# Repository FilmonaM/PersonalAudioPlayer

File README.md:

# Personal Audio Player

## Project Overview
A pocket-sized, RP2040-based audio player featuring:
- **Adafruit Feather RP2040 Adalogger** (built-in microSD slot & Li-Po charger)
- **Adafruit PCM5102A DAC** breakout board that also includes audio jack
- **2.4″ SSD1309 128×64 OLED** display (I²C)
- **Six 6 × 6 mm tactile buttons** for menu navigation & transport controls
- **One 10 kΩ potentiometer** for volume control
- no firmware...yet
---
## Case

## PCB 

## Schematic

---
## BOM

| item | quantity                                   | link                                      |
|----:|--------------------------------------------------|--------------------------------------------|
| rp2040 adalogger  | 1 |  [link](https://www.adafruit.com/product/5980?srsltid=AfmBOoo8XiFZ5O-aQrgWYq57rMrMTgJX_qIoyT-_eMKxOjlOtefi_cEq) |
| pcm5102a  | 1 |  [link](https://www.adafruit.com/product/6250?srsltid=AfmBOoqd1F7VRiLRdiD3oSu3U9al2WLzJexfJeOLYhPyQlxJku6weyUe)     |
| 2.4" oled display | 1  | [link](https://www.adafruit.com/product/6250?srsltid=AfmBOoqd1F7VRiLRdiD3oSu3U9al2WLzJexfJeOLYhPyQlxJku6weyUe)   |
| pushbutton switches   | 6  | I have my own  |
| 10kohm potentiometer | 1    | I have my own  |
| PCB | 5|     |
|lipo-battery| 1| I have my own

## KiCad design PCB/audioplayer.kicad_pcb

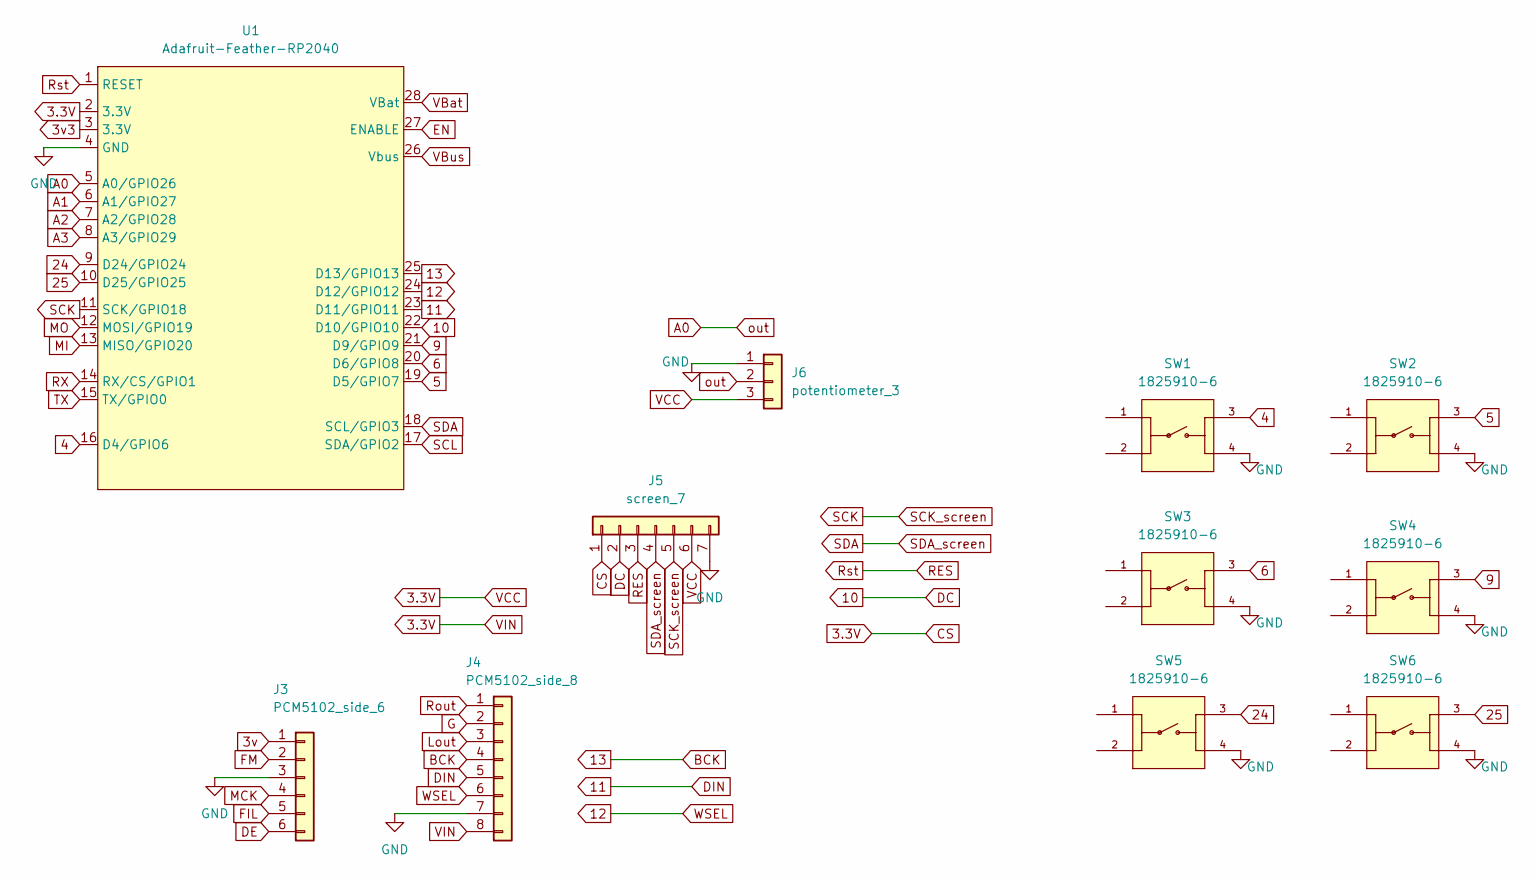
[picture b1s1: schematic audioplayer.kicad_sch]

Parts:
J3: PCM5102_side_6; PinHeader_1x06_P2.54mm_Vertical
J4: PCM5102_side_8; PinHeader_1x08_P2.54mm_Vertical
J5: screen_7; PinHeader_1x07_P2.54mm_Vertical
J6: potentiometer_3; PinHeader_1x03_P2.54mm_Vertical
SW1, SW2, SW3, SW4, SW5, SW6: 1825910-6; SW_1825910-6-4; PARTREV C10
U1: Adafruit-Feather-RP2040

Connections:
3.3V: J4.8, J5.1, J5.6, J6.3, U1.2 (3.3V)
3v: J3.1
3v3: U1.3 (3.3V)
4: SW1.3, U1.16 (D4/GPIO6)
5: SW2.3, U1.19 (D5/GPIO7)
6: SW3.3, U1.20 (D6/GPIO8)
9: SW4.3, U1.21 (D9/GPIO9)
10: J5.2, U1.22 (D10/GPIO10)
11: J4.5, U1.23 (D11/GPIO11)
12: J4.6, U1.24 (D12/GPIO12)
13: J4.4, U1.25 (D13/GPIO13)
24: SW5.3, U1.9 (D24/GPIO24)
25: SW6.3, U1.10 (D25/GPIO25)
A0: J6.2, U1.5 (A0/GPIO26)
A1: U1.6 (A1/GPIO27)
A2: U1.7 (A2/GPIO28)
A3: U1.8 (A3/GPIO29)
DE: J3.6
EN: U1.27 (ENABLE)
FIL: J3.5
FM: J3.2
G: J4.2
GND: J3.3, J4.7, J5.7, J6.1, SW1.4, SW2.4, SW3.4, SW4.4, SW5.4, SW6.4, U1.4 (GND)
Lout: J4.3
MCK: J3.4
MI: U1.13 (MISO/GPIO20)
MO: U1.12 (MOSI/GPIO19)
RES: J5.3, U1.1 (RESET)
RX: U1.14 (RX/CS/GPIO1)
Rout: J4.1
SCK: J5.5, U1.11 (SCK/GPIO18)
SCL: U1.17 (SDA/GPIO2)
SDA: J5.4, U1.18 (SCL/GPIO3)
TX: U1.15 (TX/GPIO0)
VBat: U1.28 (VBat)
VBus: U1.26 (Vbus)

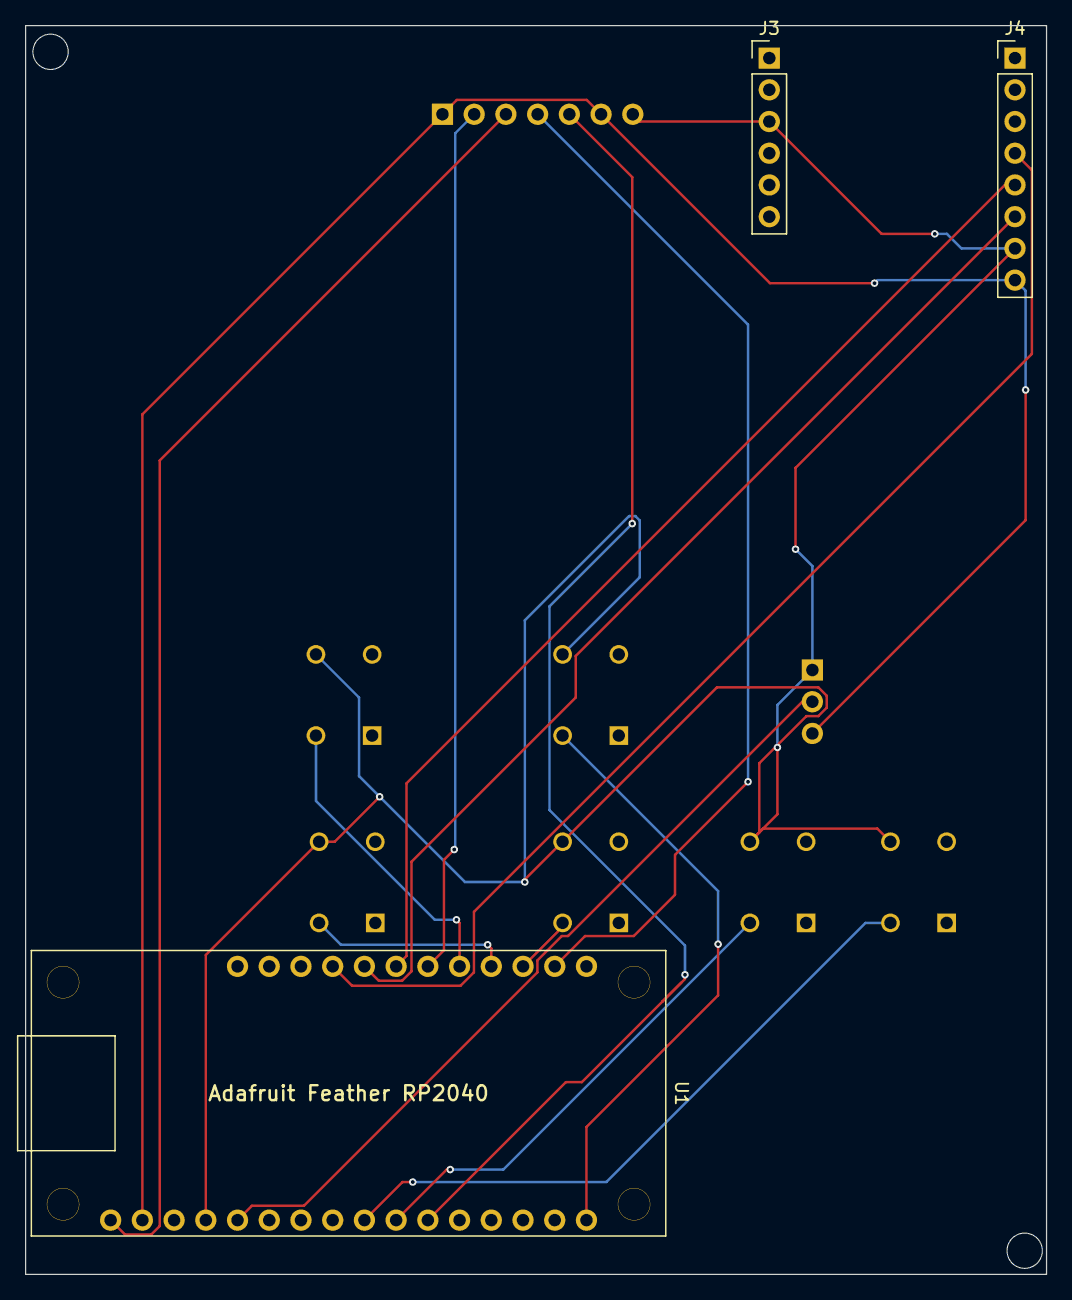
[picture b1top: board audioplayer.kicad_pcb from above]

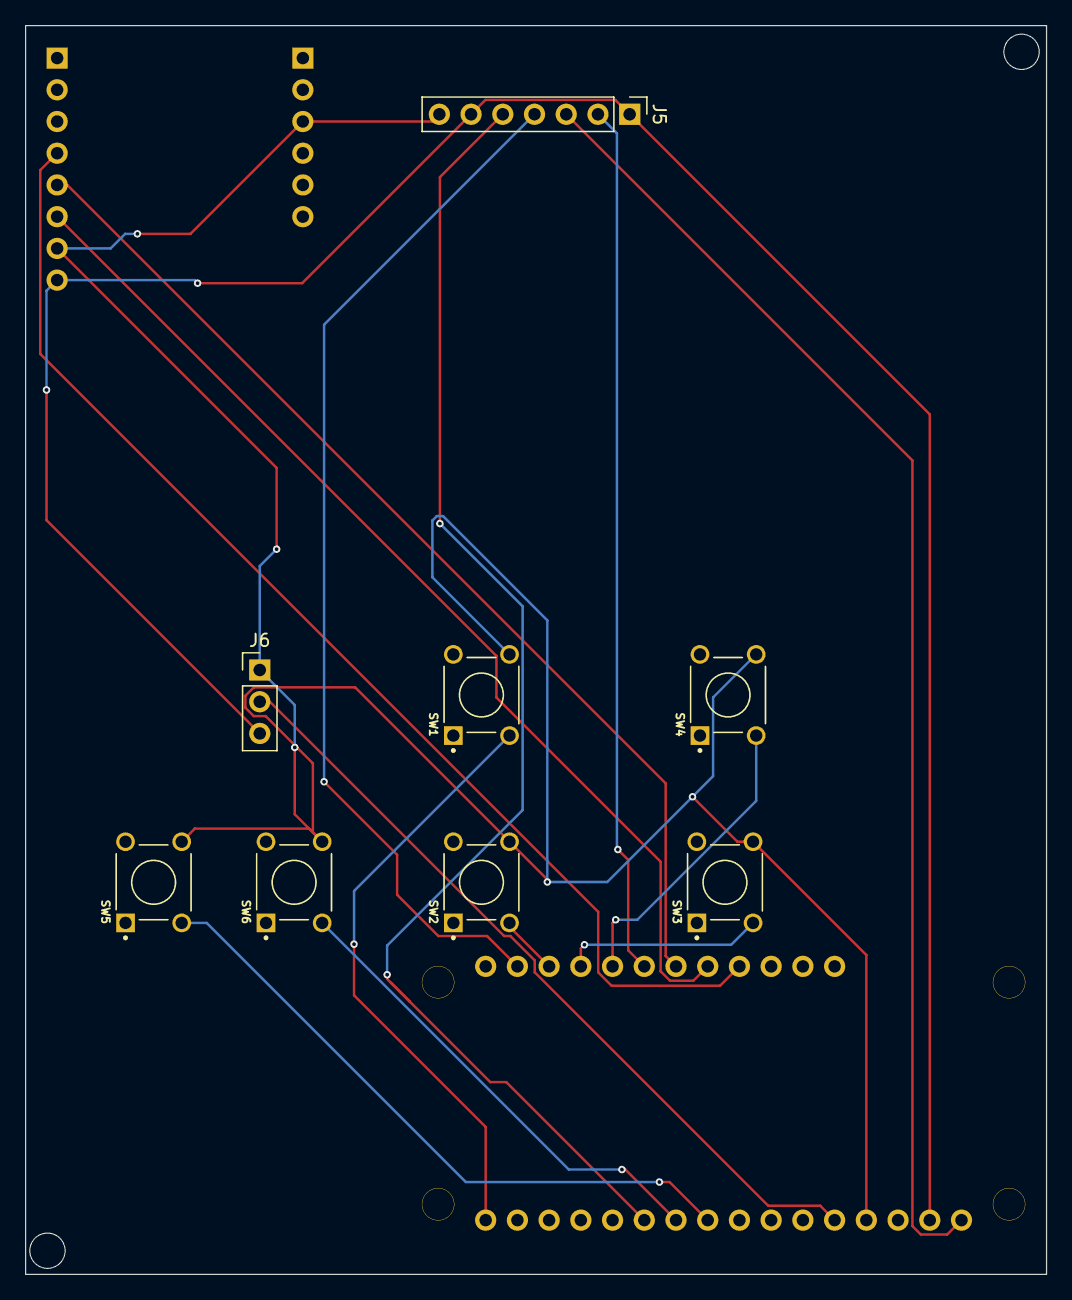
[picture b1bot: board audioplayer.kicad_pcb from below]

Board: 2 copper layers, 81.8 x 100.0 mm, 11 parts (8 on the bottom side), 16 nets.

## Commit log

2025-08-01 finalizing
